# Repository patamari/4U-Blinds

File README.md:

# 4U-Blinds
4U port of MI Blinds, Quad Voltage Controlled Polarizer

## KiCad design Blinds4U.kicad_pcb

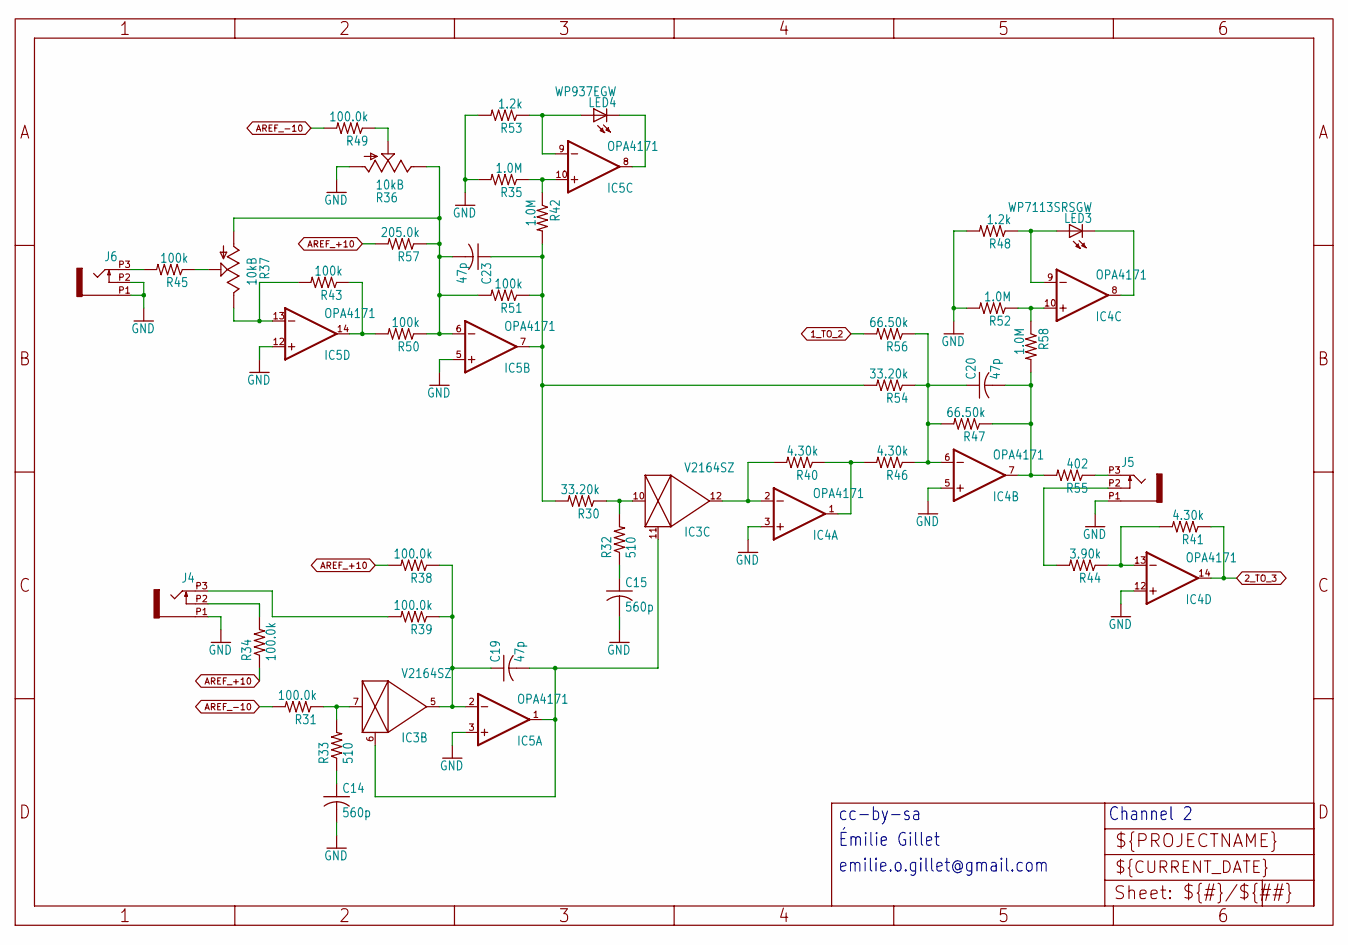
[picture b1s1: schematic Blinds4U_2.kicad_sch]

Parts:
C14, C15: 560p; C0603
C19, C20, C23: 47p; C0603
IC3: V2164SZ; SOIC16N
IC4, IC5: OPA4171; TSSOP14
J4, J5, J6: PJ301_THONKICONN6; WQP_PJ_301M6
LED3: WP7113SRSGW; LED5MM
LED4: WP937EGW; LED3MM
R30, R54: 33.20k; R0603
R31, R34, R38, R39, R49: 100.0k; R0603
R32, R33: 510; R0603
R35, R42, R52, R58: 1.0M; R0603
R36: 10kB; ALPS_POT_VERTICAL_PS
R37: 10kB; ALPS_POT_VERTICAL
R40, R41, R46: 4.30k; R0603
R43, R45, R50, R51: 100k; R0603
R44: 3.90k; R0603
R47, R56: 66.50k; R0603
R48, R53: 1.2k; R0603
R55: 402; R0603
R57: 205.0k; R0603

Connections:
1_TO_2: R56.2; also elsewhere on the board
2_TO_3: IC4.14 (OUT), R41.1; also elsewhere on the board
AREF_+10: R34.1, R38.2, R57.2; also elsewhere on the board
AREF_-10: R31.2, R49.2; also elsewhere on the board
FOO1: IC3.7 (IN), R31.1, R33.2
GAIN_2: C23.1, IC5.7 (OUT), R30.2, R42.2, R51.1, R54.2
GND: C14.2, C15.2, IC4.3 (+IN), IC4.5 (+IN), IC4.12 (+IN), IC5.3 (+IN), IC5.5 (+IN), IC5.12 (+IN), J4.P1 (1), J5.P1 (1), J6.P1 (1), J6.P2 (2), R35.2, R36.P$3 (A), R48.2, R52.2, R53.2; also elsewhere on the board
unnamed 25: J5.P3 (3), R55.1; also elsewhere on the board
unnamed: C15.1, R32.1
unnamed: IC3.10 (IN), R30.1, R32.2
unnamed: IC3.12 (OUT), IC4.2 (-IN), R40.2
unnamed: C20.1, IC4.6 (-IN), R46.1, R47.2, R54.1, R56.1
unnamed: J6.P3 (3), R45.2
unnamed: IC5.13 (-IN), R37.P$1 (E), R43.2
unnamed: IC5.14 (OUT), R43.1, R50.2
unnamed: C23.2, IC5.6 (-IN), R36.P$1 (E), R37.P$3 (A), R50.1, R51.2, R57.1
unnamed: R36.P$2 (S), R49.1
unnamed: IC5.8 (OUT), LED4.K (C)
unnamed: IC5.9 (-IN), LED4.A, R53.1
unnamed: IC4.8 (OUT), LED3.K (C)
unnamed: IC4.9 (-IN), LED3.A, R48.1
unnamed: IC4.13 (-IN), R41.2, R44.1
unnamed 57: J5.P2 (2), R44.2; also elsewhere on the board
unnamed: IC4.1 (OUT), R40.1, R46.2
unnamed: R37.P$2 (S), R45.1
unnamed: C14.1, R33.1
unnamed: C19.1, IC3.5 (OUT), IC5.2 (-IN), R38.1, R39.1
unnamed: C19.2, IC3.6 (CTRL), IC3.11 (CTRL), IC5.1 (OUT)
unnamed 63: J4.P3 (3), R39.2; also elsewhere on the board
unnamed 106: J4.P2 (2), R34.2; also elsewhere on the board
unnamed: IC4.10 (+IN), R52.1, R58.1
unnamed: IC5.10 (+IN), R35.1, R42.1
OUT2: C20.2, IC4.7 (OUT), R47.1, R55.2, R58.2

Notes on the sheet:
emilie.o.gillet@gmail.com
Émilie Gillet
Channel 2
cc-by-sa

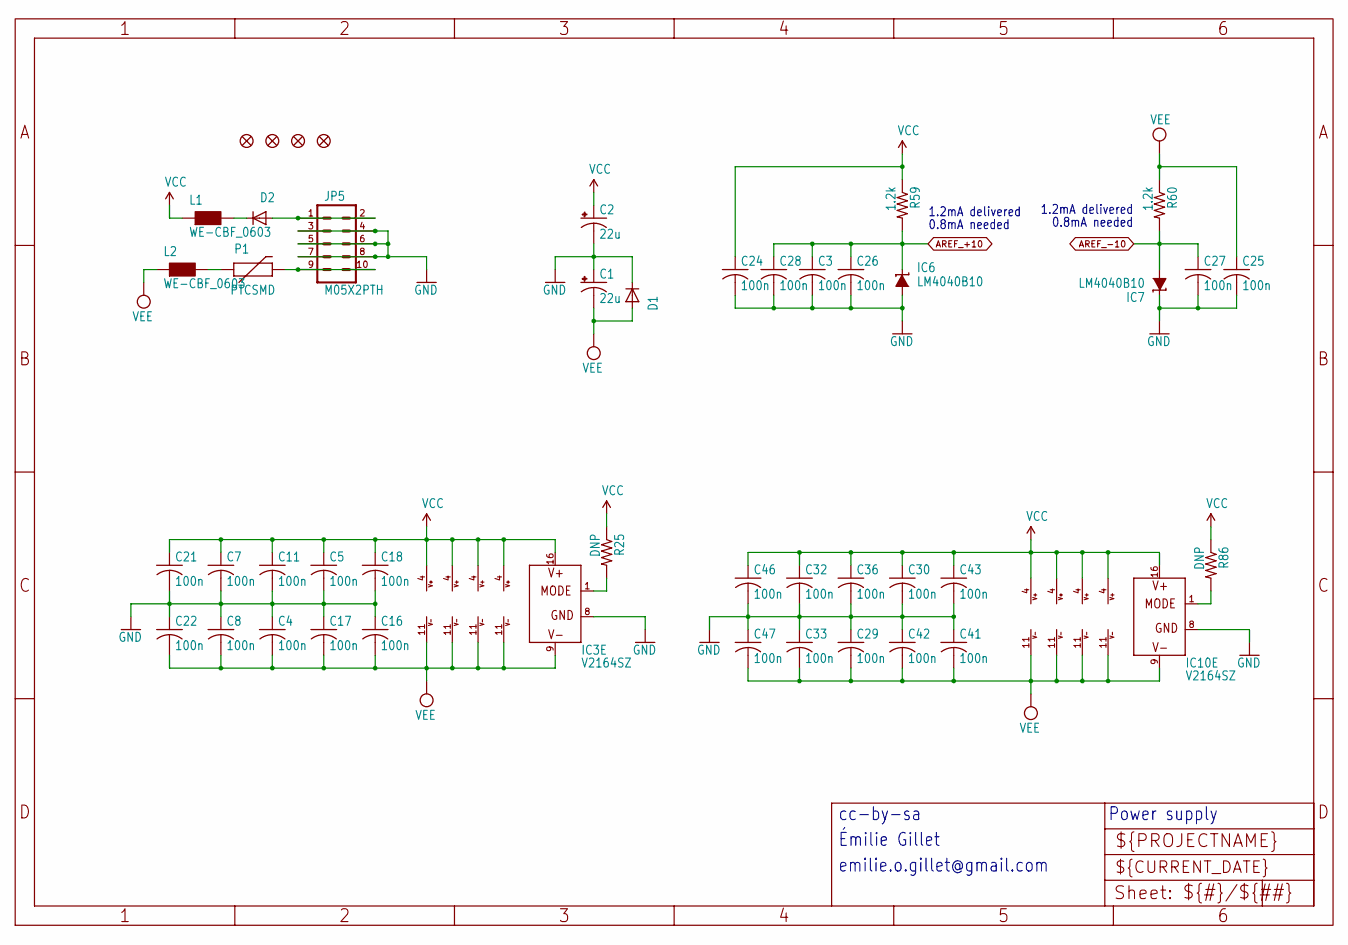
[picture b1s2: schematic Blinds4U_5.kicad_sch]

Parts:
C1, C2: 22u; PANASONIC_C
C3, C4, C5, C7, C8, C11, C16, C17, C18, C21, C22, C24, C25, C26, C27, C28, C29, C30, C32, C33, C36, C41, C42, C43, C46, C47: 100n; C0603
D1, D2: 1N5819HW; SOD123
IC1, IC2, IC4, IC5, IC8, IC9, IC11, IC12: OPA4171; TSSOP14
IC3, IC10: V2164SZ; SOIC16N
IC6, IC7: LM4040B10; DBZ_R-PDSO-G3
JP1, JP2, JP3, JP4: FIDUCIAL1X2; FIDUCIAL-1X2
JP5: M05X2PTH; AVR_ICSP
L1, L2: WE-CBF_0603; 0603
P1: PTCSMD; PTC-1206
R25, R86: DNP; R0603
R59, R60: 1.2k; R0603

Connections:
AREF_+10: C3.1, C26.1, C28.1, IC6.1 (C), R59.2; also elsewhere on the board
AREF_-10: C27.1, IC7.2 (A), R60.2; also elsewhere on the board
GND: C1.1, C1.+, C2.2, C2.-, C3.2, C4.1, C5.2, C7.2, C8.1, C11.2, C16.1, C17.1, C18.2, C21.2, C22.1, C24.2, C25.2, C26.2, C27.2, C28.2, C29.1, C30.2, C32.2, C33.1, C36.2, C41.1, C42.1, C43.2, C46.2, C47.1, D1.C, IC3.8 (GND), IC6.2 (A), IC7.1 (C), IC10.8 (GND), JP5.3, JP5.4, JP5.5, JP5.6, JP5.7, JP5.8; also elsewhere on the board
unnamed: IC3.1 (MODE), R25.2
unnamed: D2.A, JP5.1, JP5.2
unnamed: JP5.9, JP5.10, P1.2
unnamed: L2.2, P1.1
unnamed: D2.C, L1.2
unnamed: IC10.1 (MODE), R86.2
VCC: C2.1, C2.+, C5.1, C7.1, C11.1, C18.1, C21.1, C24.1, C30.1, C32.1, C36.1, C43.1, C46.1, IC1.4 (V+), IC2.4 (V+), IC3.16 (V+), IC4.4 (V+), IC5.4 (V+), IC8.4 (V+), IC9.4 (V+), IC10.16 (V+), IC11.4 (V+), IC12.4 (V+), L1.1, R25.1, R59.1, R86.1
VEE: C1.2, C1.-, C4.2, C8.2, C16.2, C17.2, C22.2, C25.1, C29.2, C33.2, C41.2, C42.2, C47.2, D1.A, IC1.11 (V-), IC2.11 (V-), IC3.9 (V-), IC4.11 (V-), IC5.11 (V-), IC8.11 (V-), IC9.11 (V-), IC10.9 (V-), IC11.11 (V-), IC12.11 (V-), L2.1, R60.1

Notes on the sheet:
cc-by-sa
emilie.o.gillet@gmail.com
1.2mA delivered
0.8mA needed
Émilie Gillet
Power supply

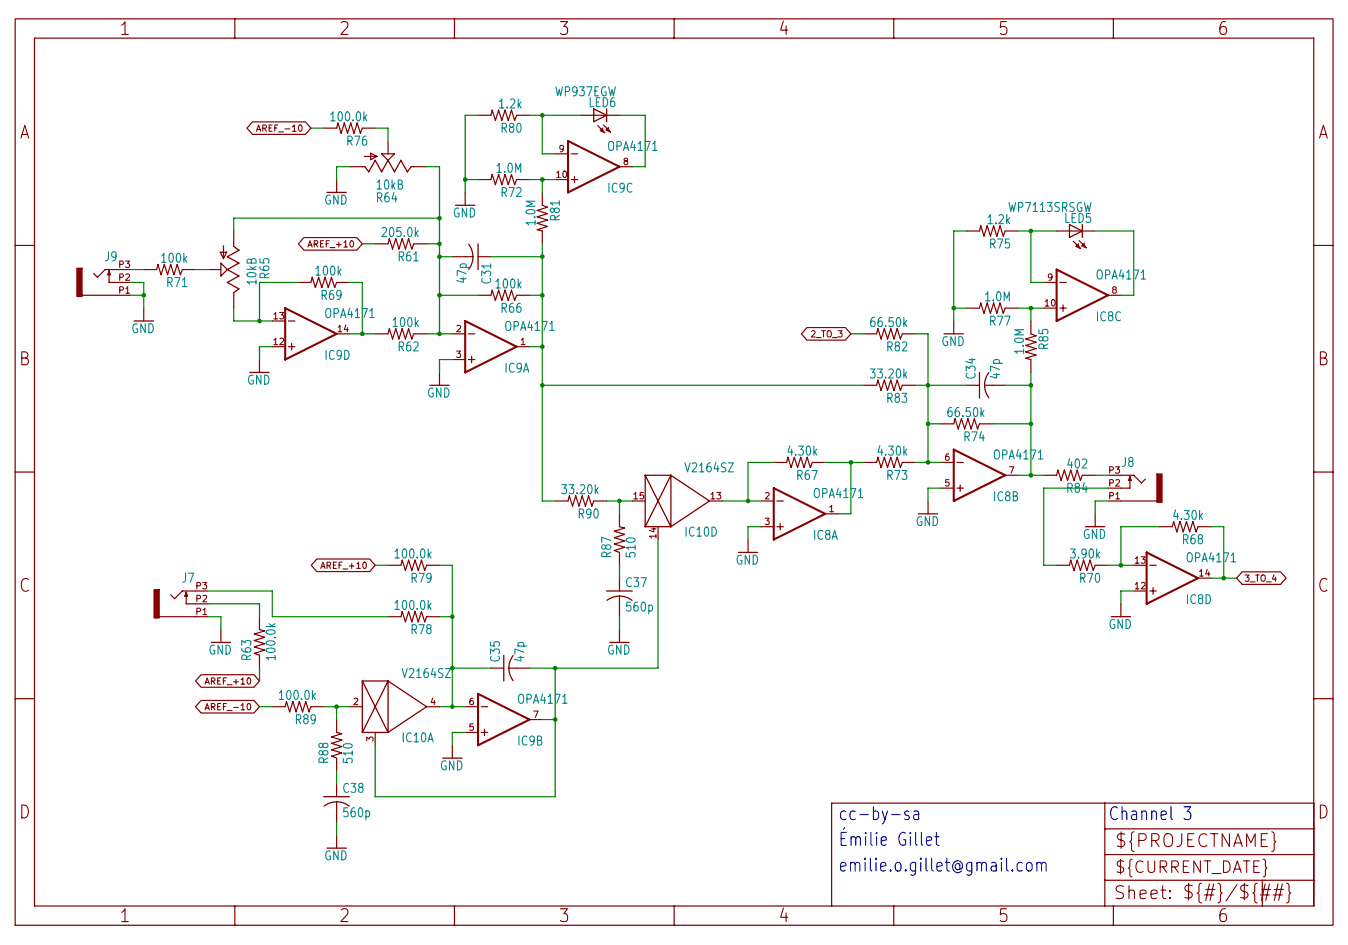
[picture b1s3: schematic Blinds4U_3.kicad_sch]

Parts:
C31, C34, C35: 47p; C0603
C37, C38: 560p; C0603
IC8, IC9: OPA4171; TSSOP14
IC10: V2164SZ; SOIC16N
J7, J8, J9: PJ301_THONKICONN6; WQP_PJ_301M6
LED5: WP7113SRSGW; LED5MM
LED6: WP937EGW; LED3MM
R61: 205.0k; R0603
R62, R66, R69, R71: 100k; R0603
R63, R76, R78, R79, R89: 100.0k; R0603
R64: 10kB; ALPS_POT_VERTICAL_PS
R65: 10kB; ALPS_POT_VERTICAL
R67, R68, R73: 4.30k; R0603
R70: 3.90k; R0603
R72, R77, R81, R85: 1.0M; R0603
R74, R82: 66.50k; R0603
R75, R80: 1.2k; R0603
R83, R90: 33.20k; R0603
R84: 402; R0603
R87, R88: 510; R0603

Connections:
2_TO_3: R82.2; also elsewhere on the board
3_TO_4: IC8.14 (OUT), R68.1; also elsewhere on the board
AREF_+10: R61.2, R63.1, R79.2; also elsewhere on the board
AREF_-10: R76.2, R89.2; also elsewhere on the board
FOO2: IC10.2 (IN), R88.2, R89.1
GAIN_3: C31.1, IC9.1 (OUT), R66.1, R81.2, R83.2, R90.2
GND: C37.2, C38.2, IC8.3 (+IN), IC8.5 (+IN), IC8.12 (+IN), IC9.3 (+IN), IC9.5 (+IN), IC9.12 (+IN), J7.P1 (1), J8.P1 (1), J9.P1 (1), J9.P2 (2), R64.P$3 (A), R72.2, R75.2, R77.2, R80.2; also elsewhere on the board
unnamed 42: J8.P3 (3), R84.1; also elsewhere on the board
unnamed: C37.1, R87.1
unnamed: IC10.15 (IN), R87.2, R90.1
unnamed: IC8.2 (-IN), IC10.13 (OUT), R67.2
unnamed: C34.1, IC8.6 (-IN), R73.1, R74.2, R82.1, R83.1
unnamed: J9.P3 (3), R71.2
unnamed: IC9.13 (-IN), R65.P$1 (E), R69.2
unnamed: IC9.14 (OUT), R62.2, R69.1
unnamed: C31.2, IC9.2 (-IN), R61.1, R62.1, R64.P$1 (E), R65.P$3 (A), R66.2
unnamed: R64.P$2 (S), R76.1
unnamed: IC9.8 (OUT), LED6.K (C)
unnamed: IC9.9 (-IN), LED6.A, R80.1
unnamed: IC8.8 (OUT), LED5.K (C)
unnamed: IC8.9 (-IN), LED5.A, R75.1
unnamed: IC8.13 (-IN), R68.2, R70.1
unnamed 80: J8.P2 (2), R70.2; also elsewhere on the board
unnamed: IC8.1 (OUT), R67.1, R73.2
unnamed: C38.1, R88.1
unnamed: C35.1, IC9.6 (-IN), IC10.4 (OUT), R78.1, R79.1
unnamed: C35.2, IC9.7 (OUT), IC10.3 (CTRL), IC10.14 (CTRL)
unnamed: R65.P$2 (S), R71.1
unnamed 112: J7.P3 (3), R78.2; also elsewhere on the board
unnamed 113: J7.P2 (2), R63.2; also elsewhere on the board
unnamed: IC8.10 (+IN), R77.1, R85.1
unnamed: IC9.10 (+IN), R72.1, R81.1
OUT3: C34.2, IC8.7 (OUT), R74.1, R84.2, R85.2

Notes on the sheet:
Channel 3
Émilie Gillet
cc-by-sa
emilie.o.gillet@gmail.com

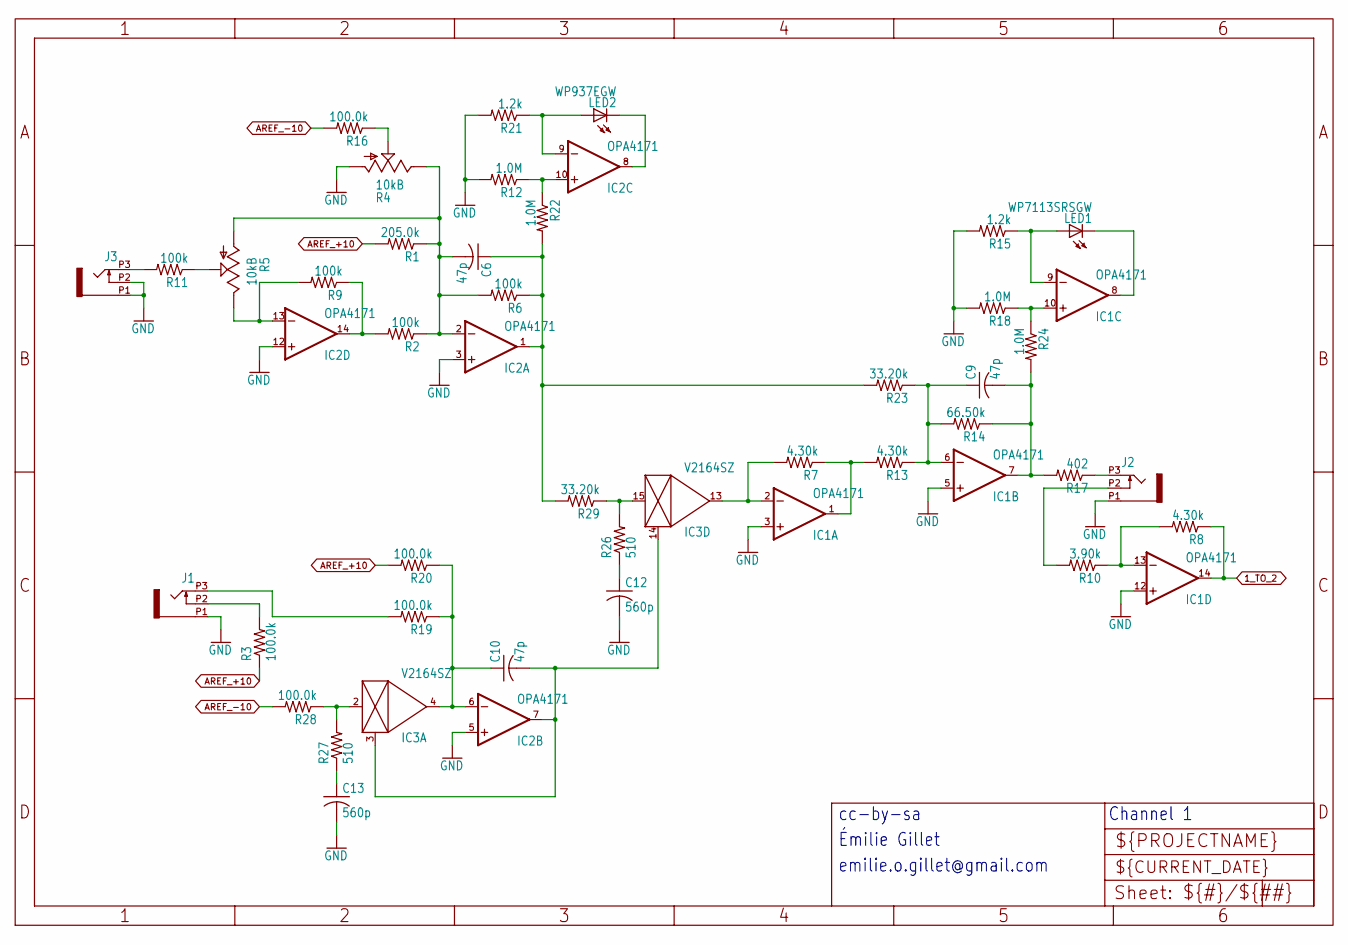
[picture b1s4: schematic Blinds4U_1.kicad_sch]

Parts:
C6, C9, C10: 47p; C0603
C12, C13: 560p; C0603
IC1, IC2: OPA4171; TSSOP14
IC3: V2164SZ; SOIC16N
J1, J2, J3: PJ301_THONKICONN6; WQP_PJ_301M6
LED1: WP7113SRSGW; LED5MM
LED2: WP937EGW; LED3MM
R1: 205.0k; R0603
R2, R6, R9, R11: 100k; R0603
R3, R16, R19, R20, R28: 100.0k; R0603
R4: 10kB; ALPS_POT_VERTICAL_PS
R5: 10kB; ALPS_POT_VERTICAL
R7, R8, R13: 4.30k; R0603
R10: 3.90k; R0603
R12, R18, R22, R24: 1.0M; R0603
R14: 66.50k; R0603
R15, R21: 1.2k; R0603
R17: 402; R0603
R23, R29: 33.20k; R0603
R26, R27: 510; R0603

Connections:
1_TO_2: IC1.14 (OUT), R8.1; also elsewhere on the board
AREF_+10: R1.2, R3.1, R20.2; also elsewhere on the board
AREF_-10: R16.2, R28.2; also elsewhere on the board
CV_IN_1: J3.P3 (3), R11.2
FOO: IC3.2 (IN), R27.2, R28.1
GAIN_1: C6.1, IC2.1 (OUT), R6.1, R22.2, R23.2, R29.2
GND: C12.2, C13.2, IC1.3 (+IN), IC1.5 (+IN), IC1.12 (+IN), IC2.3 (+IN), IC2.5 (+IN), IC2.12 (+IN), J1.P1 (1), J2.P1 (1), J3.P1 (1), J3.P2 (2), R4.P$3 (A), R12.2, R15.2, R18.2, R21.2; also elsewhere on the board
unnamed: R4.P$2 (S), R16.1
unnamed: IC1.2 (-IN), IC3.13 (OUT), R7.2
unnamed: IC2.8 (OUT), LED2.K (C)
unnamed: IC2.13 (-IN), R5.P$1 (E), R9.2
unnamed 26: J2.P3 (3), R17.1; also elsewhere on the board
unnamed: IC2.14 (OUT), R2.2, R9.1
unnamed: C6.2, IC2.2 (-IN), R1.1, R2.1, R4.P$1 (E), R5.P$3 (A), R6.2
unnamed: C9.1, IC1.6 (-IN), R13.1, R14.2, R23.1
unnamed: R5.P$2 (S), R11.1
unnamed: IC2.9 (-IN), LED2.A, R21.1
unnamed: IC1.8 (OUT), LED1.K (C)
unnamed: IC1.9 (-IN), LED1.A, R15.1
unnamed: C13.1, R27.1
unnamed 40: J1.P3 (3), R19.2; also elsewhere on the board
unnamed: IC1.13 (-IN), R8.2, R10.1
unnamed 44: J2.P2 (2), R10.2; also elsewhere on the board
unnamed: C12.1, R26.1
unnamed 73: J1.P2 (2), R3.2; also elsewhere on the board
unnamed: IC1.1 (OUT), R7.1, R13.2
unnamed: C10.1, IC2.6 (-IN), IC3.4 (OUT), R19.1, R20.1
unnamed: C10.2, IC2.7 (OUT), IC3.3 (CTRL), IC3.14 (CTRL)
unnamed: IC3.15 (IN), R26.2, R29.1
unnamed: IC1.10 (+IN), R18.1, R24.1
unnamed: IC2.10 (+IN), R12.1, R22.1
OUT1: C9.2, IC1.7 (OUT), R14.1, R17.2, R24.2

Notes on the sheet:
Channel 1
emilie.o.gillet@gmail.com
cc-by-sa
Émilie Gillet

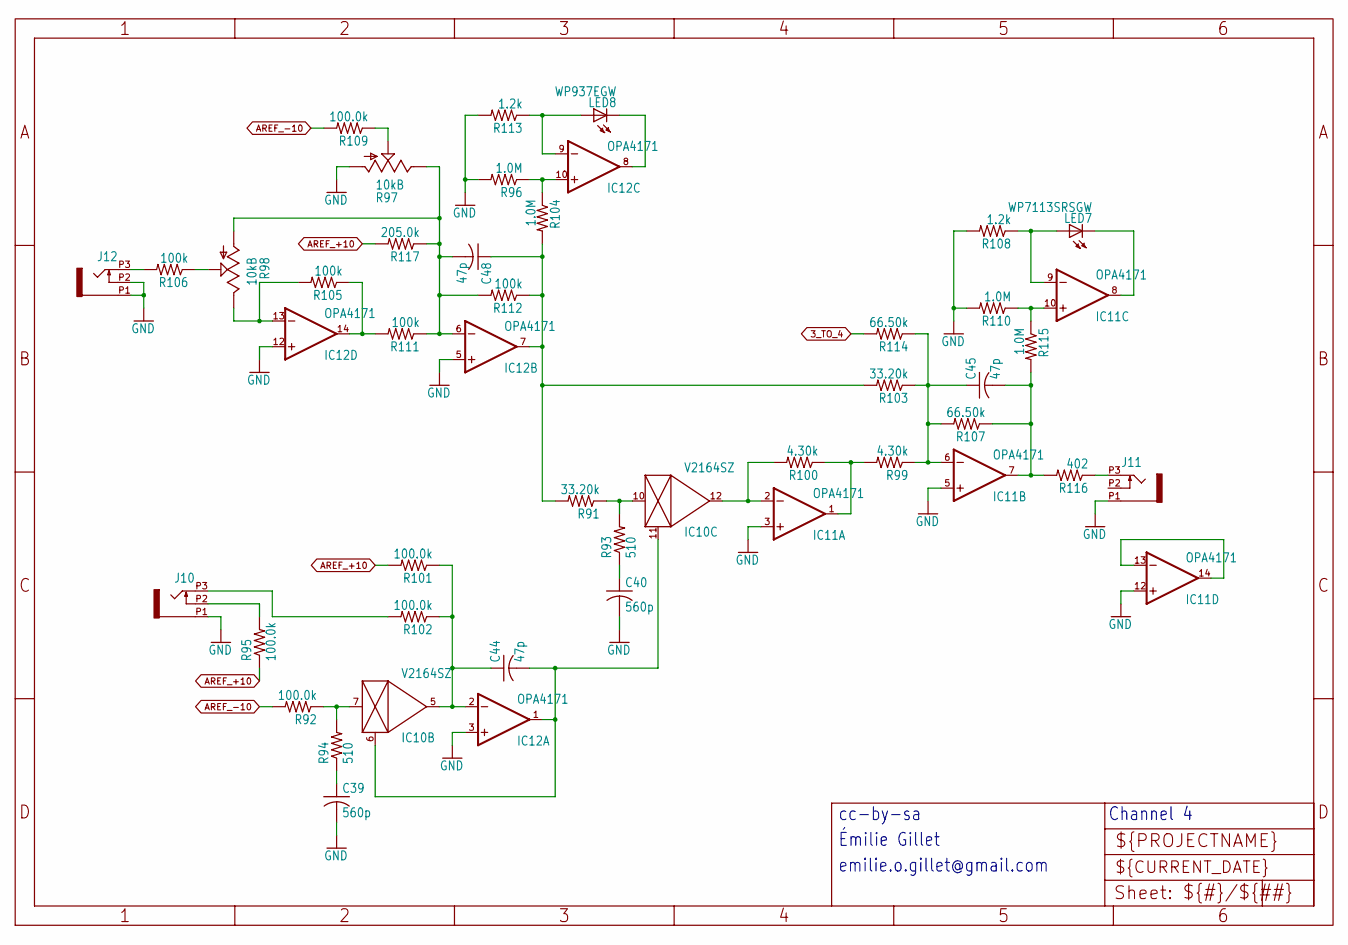
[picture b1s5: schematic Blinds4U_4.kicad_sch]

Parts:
C39, C40: 560p; C0603
C44, C45, C48: 47p; C0603
IC10: V2164SZ; SOIC16N
IC11, IC12: OPA4171; TSSOP14
J10, J11, J12: PJ301_THONKICONN6; WQP_PJ_301M6
LED7: WP7113SRSGW; LED5MM
LED8: WP937EGW; LED3MM
R91, R103: 33.20k; R0603
R92, R95, R101, R102, R109: 100.0k; R0603
R93, R94: 510; R0603
R96, R104, R110, R115: 1.0M; R0603
R97: 10kB; ALPS_POT_VERTICAL_PS
R98: 10kB; ALPS_POT_VERTICAL
R99, R100: 4.30k; R0603
R105, R106, R111, R112: 100k; R0603
R107, R114: 66.50k; R0603
R108, R113: 1.2k; R0603
R116: 402; R0603
R117: 205.0k; R0603

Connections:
3_TO_4: R114.2; also elsewhere on the board
AREF_+5: IC11.13 (-IN), IC11.14 (OUT)
AREF_+10: R95.1, R101.2, R117.2; also elsewhere on the board
AREF_-10: R92.2, R109.2; also elsewhere on the board
FOO3: IC10.7 (IN), R92.1, R94.2
GAIN_4: C48.1, IC12.7 (OUT), R91.2, R103.2, R104.2, R112.1
GND: C39.2, C40.2, IC11.3 (+IN), IC11.5 (+IN), IC11.12 (+IN), IC12.3 (+IN), IC12.5 (+IN), IC12.12 (+IN), J10.P1 (1), J11.P1 (1), J12.P1 (1), J12.P2 (2), R96.2, R97.P$3 (A), R108.2, R110.2, R113.2; also elsewhere on the board
unnamed 88: J10.P3 (3), R102.2; also elsewhere on the board
unnamed: J11.P3 (3), R116.1
unnamed: C40.1, R93.1
unnamed: IC10.10 (IN), R91.1, R93.2
unnamed: IC10.12 (OUT), IC11.2 (-IN), R100.2
unnamed: C45.1, IC11.6 (-IN), R99.1, R103.1, R107.2, R114.1
unnamed: J12.P3 (3), R106.2
unnamed: IC12.13 (-IN), R98.P$1 (E), R105.2
unnamed: IC12.14 (OUT), R105.1, R111.2
unnamed: C48.2, IC12.6 (-IN), R97.P$1 (E), R98.P$3 (A), R111.1, R112.2, R117.1
unnamed: R97.P$2 (S), R109.1
unnamed: IC12.8 (OUT), LED8.K (C)
unnamed: IC12.9 (-IN), LED8.A, R113.1
unnamed: IC11.8 (OUT), LED7.K (C)
unnamed: IC11.9 (-IN), LED7.A, R108.1
unnamed: IC11.1 (OUT), R99.2, R100.1
unnamed: R98.P$2 (S), R106.1
unnamed: C39.1, R94.1
unnamed: C44.1, IC10.5 (OUT), IC12.2 (-IN), R101.1, R102.1
unnamed: C44.2, IC10.6 (CTRL), IC10.11 (CTRL), IC12.1 (OUT)
unnamed 114: J10.P2 (2), R95.2; also elsewhere on the board
unnamed: IC11.10 (+IN), R110.1, R115.1
unnamed: IC12.10 (+IN), R96.1, R104.1
OUT4: C45.2, IC11.7 (OUT), R107.1, R115.2, R116.2

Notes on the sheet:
Émilie Gillet
cc-by-sa
Channel 4
emilie.o.gillet@gmail.com

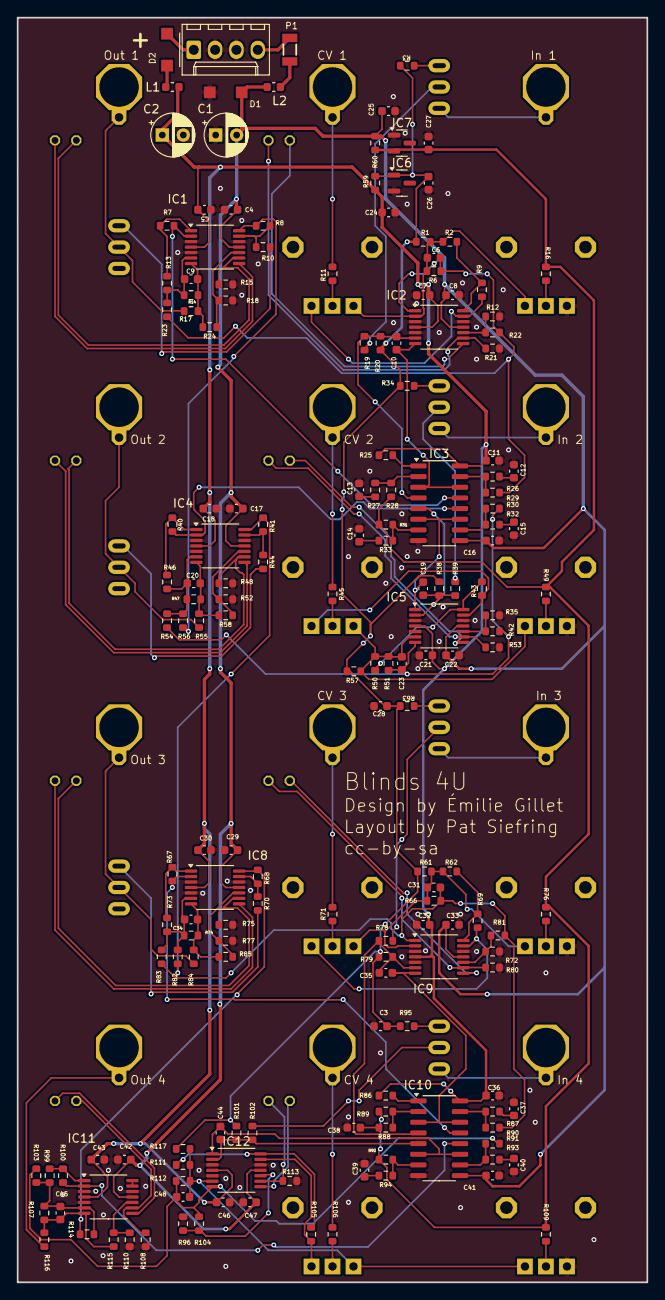
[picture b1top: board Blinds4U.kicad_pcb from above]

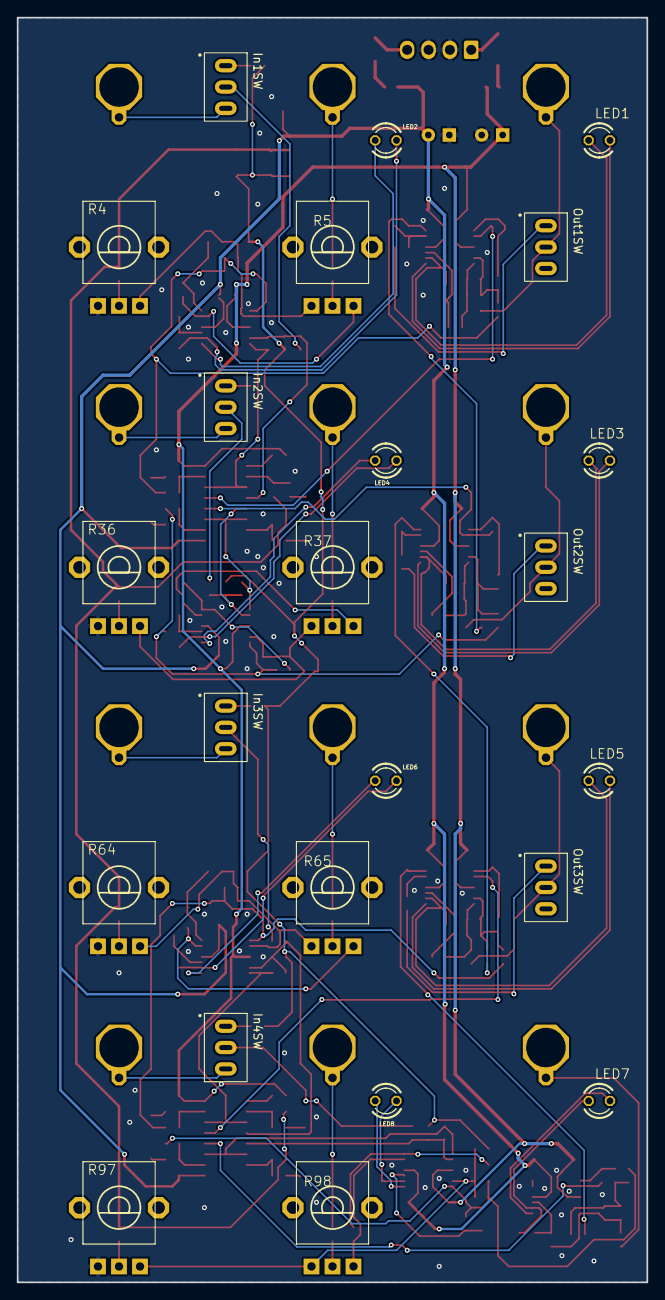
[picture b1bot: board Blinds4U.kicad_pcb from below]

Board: 2 copper layers, 74.9 x 150.5 mm, 197 parts (23 on the bottom side), 118 nets.

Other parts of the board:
In1SW, In2SW, In3SW, In4SW: SubMiniSPDT2.54mm; SubMiniSwitch2.54mm
Out1SW, Out2SW, Out3SW: SubMiniSPDT2.54mm; SubMiniSwitch2.54mm

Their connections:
unnamed 25: Out2SW.2; also elsewhere on the board
unnamed 26: Out1SW.2; also elsewhere on the board
unnamed 40: In1SW.2; also elsewhere on the board
unnamed 42: Out3SW.2; also elsewhere on the board
unnamed 44: Out1SW.1; also elsewhere on the board
unnamed 57: Out2SW.1; also elsewhere on the board
unnamed 63: In2SW.2; also elsewhere on the board
unnamed 73: In1SW.1; also elsewhere on the board
unnamed 80: Out3SW.1; also elsewhere on the board
unnamed 88: In4SW.2; also elsewhere on the board
unnamed 106: In2SW.1; also elsewhere on the board
unnamed 112: In3SW.2; also elsewhere on the board
unnamed 113: In3SW.1; also elsewhere on the board
unnamed 114: In4SW.1; also elsewhere on the board
